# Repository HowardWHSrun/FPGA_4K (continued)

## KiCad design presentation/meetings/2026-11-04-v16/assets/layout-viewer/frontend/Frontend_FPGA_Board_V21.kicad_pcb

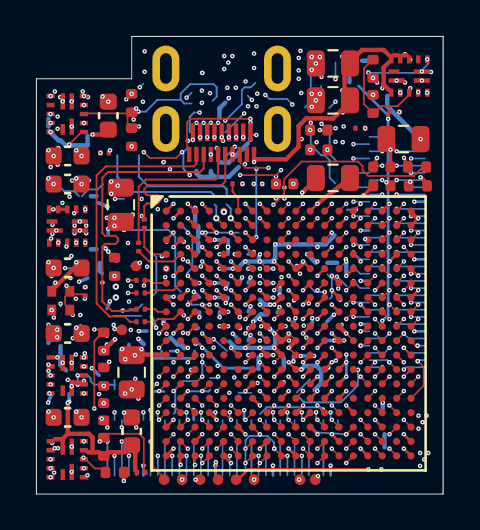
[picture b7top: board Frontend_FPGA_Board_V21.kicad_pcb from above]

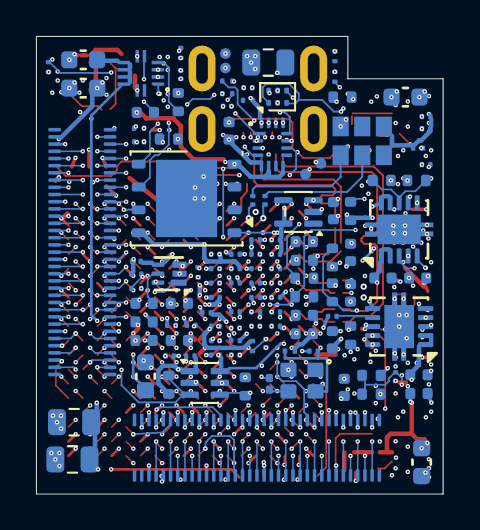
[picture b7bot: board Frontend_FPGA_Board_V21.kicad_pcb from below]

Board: 10 copper layers, 22.6 x 25.4 mm, 184 parts (122 on the bottom side), 191 nets.

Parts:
C1, C2, C12, C13, C21, C22, C85, C86: 22uF; C_0603_1608Metric
C3, C14, C23, C87: 22pF; C_0201_GRM03_Murata_0p22Gap
C4, C10, C89: 100uF; C_0805_2012Metric
C5, C6, C16, C17, C24, C25, C30, C31, C36, C37, C43, C44, C45, C47, C48, C49, C51, C54, C90, C94, C95, C96, C101: 4.7uF; C_0402_1005Metric
C7, C8, C9, C11, C18, C19, C20, C26, C27, C28, C29, C32, C33, C34, C35, C38, C39, C40, C52, C53, C55, C56, C57, C58, C80, C91, C92, C93, C97, C98, C99, C100: 470nF; C_0201_GRM03_Murata_0p22Gap
C15, C42, C59: 47uF; C_0805_2012Metric
C46, C50: 10nF; C_0201_GRM03_Murata_0p22Gap
C60, C63, C78, C79, C81, C82, C83, C88, C105, C106, C200, C201, C202, C203, C204, C205: 100nF; C_0201_GRM03_Murata_0p22Gap
C61, C84: 1uF; C_0402_1005Metric
C62: 220nF; C_0201_GRM03_Murata_0p22Gap
C75, C76, C102, C104: 22uF / 6.3V; C_0603_1608Metric
C77: 22nF / 50V; C_0402_1005Metric
C103: 470nF / 6.3V; C_0201_GRM03_Murata_0p22Gap
C206, C207, C208: 22uF / 10V; C_0805_2012Metric
J1, J2: DF40C-70DS-0.4V(51); Hirose_DF40C-70DS-0.4V_2x35_P0.4mm
J3: Micro-HDMI 467651001; Molex_MicroHDMI_46765_1xxx
L1, L2, L3, L4: MPZ0603S121HT000; TDK_MPZ0603S121HT000_0201_Land_0p25x0p30_Gap0p30
R1, R4, R5, R41, R55, R59: 200k; R_0402_1005Metric
R2: 301k; R_0402_1005Metric
R3, R9, R11, R12, R14, R17, R18, R19, R22, R38, R43, R58: 4.99k; R_0402_1005Metric
R7: 150k; R_0402_TE_CPF_Reflow_0p50Gap
R8: 100k; R_0402_TE_CPF_Reflow_0p50Gap
R10: 1.3k; R_0402_1005Metric
R13: 2.49k; R_0402_1005Metric
R16: 100R; R_0201_ERA1A_Panasonic_0p30Gap
R20, R21, R49, R50: 4.7k; R_0201_ERA1A_Panasonic_0p30Gap
R25: 470R; R_0402_1005Metric
R27: 1k; R_0201_ERA1A_Panasonic_0p30Gap
R37: 24k / 1%; R_0402_1005Metric
R42: 150k; R_0402_1005Metric
R44: 33R; R_0201_0603Metric
R45: 4.64k; R_0201_ERA1A_Panasonic_0p30Gap
R46, R47, R48: 10k; R_0201_ERA1A_Panasonic_0p30Gap
R51, R52, R53: 47k; R_0201_ERA1A_Panasonic_0p30Gap
R54: 22k; R_0201_ERA1A_Panasonic_0p30Gap
R57: 10k; R_0402_1005Metric
R60: 44.2k; R_0402_1005Metric
TP1, TP2, TP3, TP4, TP5, TP6, TP7, TP8, TP9, TP10, TP11, TP12, TP13, TP14: 0.6mm COPPER; TestPoint_Pad_D0.6mm_Edge_NoPaste
U1: XC7A35T-2CSG325I; Xilinx_CSG325
U2, U3, U4, U13, U16: MPM3834CGPA; MPM3834C_ECLGA14_2.5x2.5mm
U5, U6: TPS74801DRCRM3; VSON-10-1EP_3x3mm_P0.5mm_EP1.65x2.4mm
U7: W25Q128JWPIQ; Winbond_WSON8_6x5mm_P
U8: SN74AVC4T774RSVR / SPI x1; TI_RSV_UQFN16_1.8x2.6mm_P0.4mm
U10: MP5077GG-Z; MPS_MP5077_QFN12_2x2mm_P0.4mm
U11: 74AUP2G07GM / dual reset OD; Nexperia_SOT886_XSON6_1x1.45mm
U12: TPS389001 / timed rail-ready reset; TI_DSE0006A_WSON6_1p5x1p5_P0p5_Manufacturer
U14: SN74AUP1G14 / SPI OE; TI_DCK_SC70_5
U15: SN74AXC1T45DCKR; SOT-363_SC-70-6
Y1: AX3DAF1-125.0000T3 / 125 MHz; Abracon_AX3_3225_6pin
Y2: SiT1615A / 25 MHz / 1.5 V; SiTime_2016_4pin

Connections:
1V4_GTP_IN: C43.2, C47.2, C86.1, C87.1, R41.1, U5.1 (IN), U5.2 (IN), U6.1 (IN), U6.2 (IN), U13.6 (OUT_S), U13.9 (OUT), U13.10 (OUT)
/ASIC1_CLK32MHz_Out: J1.11, U1.P15 (L11P_T1_SRCC)
/ASIC1_DATA1: J1.3, U1.M16 (L7P_T1_D09)
/ASIC1_DATA2: J1.4, U1.N18 (L10P_T1_D14)
/ASIC1_DATA3: J1.5, U1.M17 (L7N_T1_D10)
/ASIC1_DATA4: J1.6, U1.P18 (L10N_T1_D15)
/ASIC1_DATA5: J1.7, U1.N16 (L9P_T1_DQS)
/ASIC1_DATA6: J1.8, U1.L18 (L4N_T0_D05)
/ASIC1_DATA7: J1.9, U1.K15 (L5N_T0_D07)
/ASIC1_DATA8: J1.10, U1.K18 (L3N_T0_DQS_EMCCLK)
/ASIC1_READ: J1.12, U1.K17 (L4P_T0_D04)
/ASIC1_SYNC: J1.13, U1.J15 (L2P_T0_D02)
/ASIC2_CLK32MHz_Out: J1.23, U1.E16 (L14P_T2_SRCC)
/ASIC2_DATA1: J1.18, U1.H18 (L23N_T3_FWE_B)
/ASIC2_DATA2: J1.21, U1.G14 (L22P_T3_A17)
/ASIC2_DATA3: J1.16, U1.H16 (L20P_T3_A20)
/ASIC2_DATA4: J1.17, U1.H14 (IO25)
/ASIC2_DATA5: J1.20, U1.H17 (L23P_T3_FOE_B)
/ASIC2_DATA6: J1.24, U1.G16 (L20N_T3_A19)
/ASIC2_DATA7: J1.22, U1.G17 (L19P_T3_A22)
/ASIC2_DATA8: J1.19, U1.G15 (L21P_T3_DQS)
/ASIC2_READ: J1.25, U1.F14 (L22N_T3_A16)
/ASIC2_SYNC: J1.26, U1.F18 (L19N_T3_A21_VREF)
/ASIC3_CLK32MHz_Out: J1.36, U1.E15 (L13P_T2_MRCC)
/ASIC3_DATA1: J1.31, U1.F15 (L21N_T3_DQS_A18)
/ASIC3_DATA2: J1.28, U1.F17 (L24P_T3_RS1)
/ASIC3_DATA3: J1.35, U1.D14 (L12N_T1_MRCC)
/ASIC3_DATA4: J1.30, U1.E18 (L24N_T3_RS0)
/ASIC3_DATA5: J1.29, U1.E13 (L12P_T1_MRCC)
/ASIC3_DATA6: J1.32, U1.E17 (L17P_T2_A26)
/ASIC3_DATA7: J1.39, U1.D15 (L13N_T2_MRCC)
/ASIC3_DATA8: J1.33, U1.D11 (L6P_T0)
/ASIC3_READ: J1.37, U1.C11 (L4P_T0)
/ASIC3_SYNC: J1.38, U1.D18 (L17N_T2_A25)
/ASIC4_CLK32MHz_Out: J1.43, U1.D13 (L11P_T1_SRCC)
/ASIC4_DATA1: J1.44, U1.C14 (L9P_T1_DQS_AD3P)
/ASIC4_DATA2: J1.40, U1.D16 (L14N_T2_SRCC)
/ASIC4_DATA3: J1.47, U1.C13 (L11N_T1_SRCC)
/ASIC4_DATA4: J1.45, U1.C9 (L2N_T0_AD8N)
/ASIC4_DATA5: J1.49, U1.C12 (L6N_T0_VREF)
/ASIC4_DATA6: J1.42, U1.C16 (L16P_T2_A28)
/ASIC4_DATA7: J1.53, U1.B12 (L7P_T1_AD2P)
/ASIC4_DATA8: J1.46, U1.B16 (L15P_T2_DQS)
/ASIC4_READ: J1.48, U1.B15 (L9N_T1_DQS_AD3N)
/ASIC4_SYNC: J1.51, U1.A13 (L8P_T1_AD10P)
/ASIC5_CLK32MHz_Out: J2.7, U1.R2 (L13P_T2_MRCC)
/ASIC5_DATA1: J2.11, U1.N2 (L11N_T1_SRCC)
/ASIC5_DATA2: J2.6, U1.U1 (L15N_T2_DQS)
/ASIC5_DATA3: J2.4, U1.P1 (L9N_T1_DQS)
/ASIC5_DATA4: J2.3, U1.N1 (L9P_T1_DQS)
/ASIC5_DATA5: J2.5, U1.K1 (L3N_T0_DQS)
/ASIC5_DATA6: J2.12, U1.U6 (L20P_T3)
/ASIC5_DATA7: J2.13, U1.L2 (L4N_T0)
/ASIC5_DATA8: J2.10, U1.U2 (L15P_T2_DQS)
/ASIC5_READ: J2.8, U1.T2 (L14N_T2_SRCC)
/ASIC5_SYNC: J2.9, U1.M1 (L7N_T1)
/ASIC6_CLK32MHz_Out: J2.20, U1.R3 (L14P_T2_SRCC)
/ASIC6_DATA1: J2.16, U1.R1 (L13N_T2_MRCC)
/ASIC6_DATA2: J2.19, U1.M2 (L7P_T1)
/ASIC6_DATA3: J2.24, U1.T4 (L17P_T2)
/ASIC6_DATA4: J2.17, U1.K2 (L3P_T0_DQS)
/ASIC6_DATA5: J2.18, U1.T3 (L17N_T2)
/ASIC6_DATA6: J2.25, U1.L3 (L5N_T0)
/ASIC6_DATA7: J2.22, U1.U4 (L18P_T2)
/ASIC6_DATA8: J2.23, U1.P3 (L12N_T1_MRCC)
/ASIC6_READ: J2.21, U1.K3 (L4P_T0)
/ASIC6_SYNC: J2.26, U1.V6 (L23N_T3)
/ASIC7_CLK32MHz_Out: J2.31, U1.P4 (L12P_T1_MRCC)
/ASIC7_DATA1: J2.33, U1.N4 (L10N_T1)
/ASIC7_DATA2: J2.30, U1.V4 (L18N_T2)
/ASIC7_DATA3: J2.29, U1.M4 (L10P_T1)
/ASIC7_DATA4: J2.36, U1.U7 (L23P_T3)
/ASIC7_DATA5: J2.28, U1.T5 (L21N_T3_DQS)
/ASIC7_DATA6: J2.32, U1.U5 (L20N_T3)
/ASIC7_DATA7: J2.35, U1.R5 (L21P_T3_DQS)
/ASIC7_DATA8: J2.37, U1.R6 (IO25)
/ASIC7_READ: J2.39, U1.R7 (L22P_T3)
/ASIC7_SYNC: J2.38, U1.V7 (L24N_T3)
/ASIC8_CLK32MHz_Out: J2.49, U1.R16 (L14P_T2_SRCC)
/ASIC8_DATA1: J2.53, U1.R17 (L14N_T2_SRCC)
/ASIC8_DATA2: J2.46, U1.V12 (L21P_T3_DQS)
/ASIC8_DATA3: J2.40, U1.U9 (L24P_T3_A01_D17)
/ASIC8_DATA4: J2.48, U1.U12 (L22N_T3_A04_D20)
/ASIC8_DATA5: J2.47, U1.T13 (L19N_T3_A09_D25_VREF)
/ASIC8_DATA6: J2.43, U1.U11 (L23P_T3_A03_D19)
/ASIC8_DATA7: J2.45, U1.T12 (L22P_T3_A05_D21)
/ASIC8_DATA8: J2.44, U1.V11 (L23N_T3_A02_D18)
/ASIC8_READ: J2.42, U1.V9 (L24N_T3_A00_D16)
/ASIC8_SYNC: J2.51, U1.T17 (L16P_T2_CSI_B)
/CLK25_RAW: R44.1, Y2.3 (OUT)
/CLK25_VDD: C88.1, L3.2, Y2.4 (VDD)
/FB_GTP_1V4: C87.2, R41.2, R42.1, U13.5 (FB)
/FB_VIN_3V3: R59.2, R60.1, U16.5 (FB)
/FE_RESET_SHARED: J1.64, U1.A15 (L10N_T1_AD11N)
/GPIO_CMD_N: J3.14 (GPIO_CMD_N), U1.V2 (L16N_T2)
/GPIO_CMD_P: J3.12 (GPIO_CMD_P), U1.V3 (L16P_T2)
/IMP_TST_SHARED: J1.63, U1.A12 (L7N_T1_AD2N)
/NONSTIM_BOARD1_SPI_DL: J1.58, U1.B17 (L16N_T2_A27)
/NONSTIM_BOARD1_SPI_DR: J1.59, U1.B11 (L4N_T0)
/NONSTIM_BOARD2_SPI_DL: J2.63, U1.U16 (L17N_T2_A13_D29)
/NONSTIM_BOARD2_SPI_DR: J2.59, U1.T14 (L13P_T2_MRCC)
/STIM_CHIP1_SPI_DL: J1.65, U1.A9 (L3N_T0_DQS_AD1N)
/STIM_CHIP1_SPI_DR: J1.60, U1.B14 (L10P_T1_AD11P)
/STIM_CHIP2_SPI_DL: J1.62, U1.A17 (L15N_T2_DQS_ADV_B)
/STIM_CHIP3_SPI_DL: J2.56, U1.V13 (L21N_T3_DQS_A06_D22)
/STIM_CHIP4_SPI_DR: J2.61, U1.T15 (L13N_T2_MRCC)
BOARD1_CLK: J1.56, U1.C17 (L18P_T2_A24)
BOARD1_SPI_CLK: J1.54, U1.C18 (L18N_T2_A23)
BOARD2_CLK: J1.61, U1.A10 (L5N_T0_AD9N)
BOARD2_SPI_CLK: J1.55, U1.B10 (L5P_T0_AD9P)
BOARD3_CLK: J2.54, U1.V8 (L24P_T3)
BOARD3_SPI_CLK: J2.55, U1.U10 (IO25)
BOARD4_CLK: J2.52, U1.T7 (L22N_T3)
BOARD4_SPI_CLK: J2.65, U1.T18 (L15N_T2_DQS_DOUT_CSO_B)
BOOT_RAILS_PG_3V3: R9.2, TP10.1 (PAD_1), U4.11 (PG), U5.3 (PG), U12.3 (MR_PG)
BOOT_RESET_N: R47.2, U11.1 (1A_RESET_N), U11.3 (2A_RESET_N), U12.6 (RESET_N_OD), U14.2 (A_RESET_N)
CABLE_TARGET_SENSE: J3.1 (SENSE), R27.2
CHIP_RESET_SHARED: J1.52, U1.J16 (L2N_T0_D03)
CLK25_PL: R44.2, U1.N3 (L11P_T1_SRCC)
EN_GTPWR_1V5: R58.2, U1.M15 (L6N_T0_D08_VREF), U15.3 (A)
EN_GTPWR_3V3: R57.1, U13.3 (EN), U15.4 (B)
FLASH_CS_N_1V8: R22.2, U7.1, U8.11 (B2_CS)
FLASH_DQ0_1V8: R53.2, U7.5, U8.10 (B3_MOSI)
FLASH_DQ1_1V8: R51.1, U7.2, U8.9 (B4_MISO)
FLASH_HOLD_N_1V8: R21.2, U7.7
FLASH_READY_SENSE: R45.2, R46.1, U12.1 (SENSE_DIV)
FLASH_SCK_1V8: R52.1, U7.6, U8.12 (B1_SCK)
FLASH_TRANSLATOR_OE_N: R48.2, U8.7 (OE_N), U14.4 (Y_OE_N)
FLASH_WP_N_1V8: R20.2, U7.3
FPGA_DONE: R38.2, TP12.1 (PAD_1), U1.F12 (DONE_0)
FPGA_INIT_B: R18.2, TP11.1 (PAD_1), U1.T10 (INIT_B_0), U11.4 (2Y_INIT_OD)
FPGA_JTAG_TCK: J3.17 (TCK), U1.F8 (TCK_0)
FPGA_JTAG_TDI: J3.15 (TDI), U1.T9 (TDI_0)
FPGA_JTAG_TDO: J3.18 (TDO), U1.T8 (TDO_0)
FPGA_JTAG_TMS: J3.2 (TMS), U1.R8 (TMS_0)
FPGA_PROGRAM_B: R17.2, U1.P10 (PROGRAM_B_0), U11.6 (1Y_PROGRAM_OD)
FPGA_PUDC_B: R25.2, U1.J18 (L3P_T0_DQS_PUDC_B)
FPGA_QSPI_CCLK: R49.2, U1.E8 (CCLK_0), U8.1 (A1_CCLK)
FPGA_QSPI_CS_N: R19.2, U1.L15 (L6P_T0_FCS_B), U8.2 (A2_CS)
FPGA_QSPI_DQ0: R50.2, U1.K16 (L1P_T0_D00_MOSI), U8.3 (A3_MOSI)
FPGA_QSPI_DQ1: R54.1, U1.L17 (L1N_T0_D01_DIN), U8.4 (A4_MISO)
GND: C1.2, C2.2, C4.2, C5.2, C6.2, C7.2, C8.2, C9.2, C10.2, C11.2, C12.2, C13.2, C15.2, C16.2, C17.2, C18.2, C19.2, C20.2, C21.2, C22.2, C24.2, C25.2, C26.2, C27.2, C28.2, C29.2, C30.2, C31.2, C32.2, C33.2, C34.2, C35.2, C36.2, C37.2, C38.2, C39.2, C40.2, C42.2, C43.1, C44.2, C45.2, C46.2, C47.1, C48.2, C49.2, C50.2, C51.2, C52.2, C53.2, C54.2, C55.2, C56.2, C58.2, C59.2, C60.2, C61.2, C62.2, C63.2, C75.2, C76.2, C77.2, C80.2, C81.2, C82.2, C83.2, C84.2, C85.2, C86.2, C88.2, C89.2, C90.2, C91.2, C92.2, C93.2, C94.2, C95.2, C96.2, C97.2, C98.2, C99.2, C100.2, C101.2, C102.2, C103.2, C104.2, C105.2, C106.2, C206.2, C207.2, C208.2, J1.14, J1.15, J1.27, J1.34, J1.41, J1.50, J1.66, J2.14, J2.15, J2.27, J2.34, J2.41, J2.50, J2.66, J3.4 (GND), J3.7 (GND), J3.10 (GND), J3.13 (GND), J3.16 (GND), J3.SH (SHIELD), L2.1, R2.2, R5.2, R8.2, R11.2, R14.2, R37.2, R42.2, R46.2, R51.2, R52.2, R54.2, R55.2, R57.2, R60.2, TP1.1 (PAD_1), TP13.1 (PAD_1), U1.A1 (GND_[75_balls]), U1.A3 (MGTPRXN1_216), U1.A4 (MGTPRXP1_216), U1.A5 (GND), U1.A7 (GND), U1.A8 (GND), U1.A11 (GND), U1.A18 (GND), U1.B3 (GND), U1.B7 (GND), U1.B8 (GND), U1.B18 (GND), U1.C2 (GND), U1.C3 (MGTPRXN2_216), U1.C4 (MGTPRXP2_216), U1.C6 (GND), U1.C7 (GND), U1.C15 (GND), U1.D3 (GND), U1.D4 (GND), U1.D7 (GND), U1.D12 (GND), U1.E2 (GND), U1.E3 (MGTPRXN0_216), U1.E4 (MGTPRXP0_216), U1.E6 (GND), U1.E7 (GND), U1.E9 (GND), U1.E12 (CFGBVS_0), U1.F4 (GND), U1.F6 (GND), U1.F10 (GND), U1.F13 (M2_0), U1.F16 (GND), U1.G1 (GND), U1.G3 (MGTPRXN3_216), U1.G4 (MGTPRXP3_216), U1.G5 (GND), U1.G6 (GND), U1.G7 (GND), U1.G9 (GND), U1.G11 (GND), U1.G13 (GND), U1.H3 (GND), U1.H4 (GND), U1.H5 (GND), U1.H6 (GND), U1.H8 (GND), U1.H10 (GND), U1.H12 (GND), U1.J1 (GND), U1.J2 (GND), U1.J3 (GND), U1.J7 (GND), U1.J11 (GND), U1.J13 (GND), U1.J17 (GND), U1.K4 (GND), U1.K8 (GND), U1.K12 (GND), U1.K14 (GND), U1.L1 (GND), U1.L7 (GND), U1.L11 (GND), U1.L13 (GND), U1.M8 (GND), U1.M9 (DXN_0), U1.M10 (DXP_0), U1.M12 (GND), U1.M18 (GND), U1.N5 (GND), U1.N7 (GND), U1.N9 (GND), U1.N11 (GND), U1.N13 (GND), U1.N15 (GND), U1.P2 (GND), U1.P8 (GND), U1.P12 (GND), U1.R9 (GND), U1.R11 (M1_0), U1.T6 (GND), U1.T16 (GND), U1.U3 (GND), U1.U13 (GND), U1.V1 (GND), U1.V10 (GND), U1.V18 (GND), U2.2 (PGND), U2.4 (AGND), U2.7 (PGND), U2.8 (PGND), U3.2 (PGND), U3.4 (AGND), U3.7 (PGND), U3.8 (PGND), U4.2 (PGND), U4.4 (AGND), U4.7 (PGND), U4.8 (PGND), U5.6 (GND), U5.11 (GND_EP), U6.6 (GND), U6.11 (GND_EP), U7.4, U8.6 (DIR4_L), U8.8 (GND), U10.2 (GND), U11.2 (GND), U12.2 (GND), U13.2 (PGND), U13.4 (AGND), U13.7 (PGND), U13.8 (PGND), U14.3 (GND), U15.2 (GND), U16.2 (PGND), U16.4 (AGND), U16.7 (PGND), U16.8 (PGND), Y1.3 (GND), Y2.2 (GND)
GNDADC_XADC: C57.2, L2.2, U1.J9 (GNDADC_0), U1.K9 (VREFN_0), U1.K10 (VP_0), U1.L9 (VN_0), U1.L10 (VREFP_0)
GTP_REFCLK1_N: C79.2, U1.B5 (MGTREFCLK1N_216)
GTP_REFCLK1_P: C78.2, U1.B6 (MGTREFCLK1P_216)
GTP_TX0_N: C201.1, J3.5 (TX0_REC_N)
GTP_TX0_P: C200.1, J3.3 (TX0_REC_P)
MGTAVCC_1V0: C45.1, C51.1, C52.1, C53.1, R10.1, TP7.1 (PAD_1), U1.B4 (MGTAVCC), U1.C5 (MGTAVCC), U1.E5 (MGTAVCC), U1.F5 (MGTAVCC), U5.9 (OUT), U5.10 (OUT)
MGTAVTT_1V2: C49.1, C54.1, C55.1, C56.1, R13.1, R16.1, TP8.1 (PAD_1), U1.A2 (MGTAVTT), U1.C1 (MGTAVTT), U1.E1 (MGTAVTT), U1.F3 (MGTAVTT), U1.G2 (MGTAVTT), U6.9 (OUT), U6.10 (OUT)
unnamed: C203.1, J3.8 (TX1_REC_N)
unnamed: C202.1, J3.6 (TX1_REC_P)
unnamed: C205.1, J3.11 (TX2_REC_N)
unnamed: C204.1, J3.9 (TX2_REC_P)
unnamed: C201.2, U1.H1 (MGTPTXN0_216)
unnamed: C203.2, U1.F1 (MGTPTXN1_216)
unnamed: C205.2, U1.D1 (MGTPTXN2_216)
unnamed: C200.2, U1.H2 (MGTPTXP0_216)
unnamed: C202.2, U1.F2 (MGTPTXP1_216)
unnamed: C204.2, U1.D2 (MGTPTXP2_216)
unnamed: R16.2, U1.A6 (MGTRREF_216)
unnamed: C3.2, R1.2, R2.1, U2.5 (FB)
unnamed: C14.2, R4.2, R5.1, R55.1, U3.5 (FB)
unnamed: C23.2, R7.2, R8.1, U4.5 (FB)
unnamed: R10.2, R11.1, U5.8 (FB)
unnamed: C46.1, U5.7 (SS)
unnamed: R13.2, R14.1, U6.8 (FB)
unnamed: C50.1, U6.7 (SS)
unnamed: R37.1, U10.4 (ILIM)
unnamed: C77.1, U10.5 (SS)
unnamed: C84.1, U12.5 (CT)
OSC125_3V3: C80.1, C81.1, L4.2, Y1.1 (OE), Y1.6 (VDD)
OSC125_N: C79.1, Y1.5 (OUTN)
OSC125_P: C78.1, Y1.4 (OUTP)
PG_CORE_1V0: R3.2, U2.11 (PG), U3.3 (EN), U4.3 (EN), U10.1 (EN)
PG_GTP_1V4: R43.2, U6.5 (EN), U13.11 (PG)
PG_MGT_1V2: R12.2, U5.5 (EN), U6.3 (PG)
SPI_LATCH_SHARED: J1.67, U1.A14 (L8N_T1_AD10N)
STIM_CHB_SHARED: J2.64, U1.U15 (L17P_T2_A14_D30)
STIM_CHIP2_SPI_DR: J1.57, U1.B9 (L3P_T0_DQS_AD1P)
STIM_CHIP3_SPI_DR: J2.57, U1.R13 (L19P_T3_A10_D26)
STIM_CHIP4_SPI_DL: J2.62, U1.V16 (L18P_T2_A12_D28)
STIM_CLK_SHARED: J2.67, U1.V17 (L18N_T2_A11_D27)
STIM_EN_SHARED: J2.58, U1.V14 (L20N_T3_A07_D23)
STIM_START_SHARED: J2.60, U1.U14 (L20P_T3_A08_D24)
SWITCHED_3V3: C76.1, C104.1, C106.1, L4.1, TP3.1 (PAD_1), U10.7 (VOUT), U10.8 (VOUT), U10.9 (VOUT), U10.10 (VOUT), U15.6 (VCCB)
VCCADC_1V8: C57.1, L1.2, U1.J10 (VCCADC_0)
VCCAUX_1V8: C13.1, C14.1, C15.1, C16.1, C17.1, C18.1, C19.1, C20.1, C58.1, C59.1, C60.1, C62.1, C94.1, C95.1, C96.1, C97.1, C98.1, C99.1, C100.1, L1.1, R4.1, R17.1, R18.1, R20.1, R21.1, R22.1, R27.1, R38.1, R45.1, R49.1, R53.1, TP5.1 (PAD_1), TP9.1 (PAD_1), U1.E10 (VCCO_0), U1.E11 (VCCBATT_0), U1.G12 (VCCAUX_[5_balls]), U1.H13 (VCCAUX), U1.K13 (VCCAUX), U1.M13 (VCCAUX), U1.P13 (VCCAUX), U1.R10 (VCCO_0), U1.R12 (M0_0), U3.6 (OUT_S), U3.9 (OUT), U3.10 (OUT), U7.8, U8.13 (VCCB_1V8)
VCCINT_1V0: C2.1, C3.1, C4.1, C5.1, C6.1, C7.1, C8.1, C9.1, C10.1, C11.1, C89.1, C90.1, C91.1, C92.1, C93.1, R1.1, TP4.1 (PAD_1), U1.F7 (VCCINT_1V0), U1.F9 (VCCINT_1V0), U1.F11 (VCCBRAM/VCCINT_[21_balls]), U1.G8 (VCCINT_1V0), U1.G10 (VCCBRAM_1V0), U1.H7 (VCCINT_1V0), U1.H9 (VCCINT_1V0), U1.H11 (VCCBRAM_1V0), U1.J8 (VCCINT_1V0), U1.J12 (VCCINT_1V0), U1.K7 (VCCINT_1V0), U1.K11 (VCCINT_1V0), U1.L8 (VCCINT_1V0), U1.L12 (VCCINT_1V0), U1.M7 (VCCINT_1V0), U1.M11 (VCCINT_1V0), U1.N8 (VCCINT_1V0), U1.N10 (VCCINT_1V0), U1.N12 (VCCINT_1V0), U1.P9 (VCCINT_1V0), U1.P11 (VCCINT_1V0), U2.6 (OUT_S), U2.9 (OUT), U2.10 (OUT)
VCCO_1V5: C22.1, C23.1, C24.1, C25.1, C26.1, C27.1, C28.1, C29.1, C30.1, C31.1, C32.1, C33.1, C34.1, C35.1, C36.1, C37.1, C38.1, C39.1, C40.1, C42.1, C61.1, C63.1, C101.1, C105.1, L3.1, R7.1, R19.1, R25.1, R48.1, R50.1, R58.1, TP6.1 (PAD_1), U1.A16 (VCCO), U1.B13 (VCCO), U1.C10 (VCCO), U1.D17 (VCCO), U1.E14 (VCCO), U1.G18 (VCCO), U1.H15 (VCCO), U1.L6 (VCCO), U1.L16 (VCCO), U1.M3 (VCCO), U1.P7 (VCCO), U1.P17 (VCCO), U1.R4 (VCCO), U1.R14 (VCCO), U1.T1 (VCCO), U1.T11 (VCCO), U1.U8 (VCCO), U1.U18 (VCCO), U1.V5 (VCCO), U1.V15 (VCCO), U4.6 (OUT_S), U4.9 (OUT), U4.10 (OUT), U8.5 (DIR3_H), U8.14 (VCCA_1V5), U8.15 (DIR1_H), U8.16 (DIR2_H), U14.5 (VCC_1V5), U15.1 (VCCA), U15.5 (DIR)
VIN_3V3: C1.1, C12.1, C21.1, C44.1, C48.1, C75.1, C82.1, C83.1, C85.1, C102.1, C103.1, C208.1, J1.68, R3.1, R9.1, R12.1, R43.1, R47.1, R59.1, TP2.1 (PAD_1), U2.3 (EN), U2.12 (IN), U2.13 (IN), U2.14 (IN), U3.12 (IN), U3.13 (IN), U3.14 (IN), U4.12 (IN), U4.13 (IN), U4.14 (IN), U5.4 (BIAS), U6.4 (BIAS), U10.3 (VCC), U10.6 (VIN), U10.11 (VIN), U11.5 (VCC_3V3), U12.4 (VDD_3V3), U13.12 (IN), U13.13 (IN), U13.14 (IN), U16.6 (OUT_S), U16.9 (OUT), U16.10 (OUT)
VIN_5V: C206.1, C207.1, J3.19 (5V_IN), TP14.1 (PAD_1), U16.3 (EN), U16.12 (IN), U16.13 (IN), U16.14 (IN)
